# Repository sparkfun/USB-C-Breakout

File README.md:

SparkFun USB-C Serial Breakout
========================================

[*SparkFun Serial Basic Breakout [BOB-15100]*](https://www.sparkfun.com/products/15100)

This is a simple breakout for the USB-C connector.  USB-C is able to
provide up to 1.5 Amps of power and unlike its predecessor is
_reversable_, meaning you won't ever plug a cable in wrong again. 

Repository Contents
-------------------

* **/Hardware** - Eagle design files (.brd, .sch)
* **/Production** - Production panel files (.brd)

License Information
-------------------

This product is _**open source**_! 

Distributed as-is; no warranty is given.

- Your friends at SparkFun.

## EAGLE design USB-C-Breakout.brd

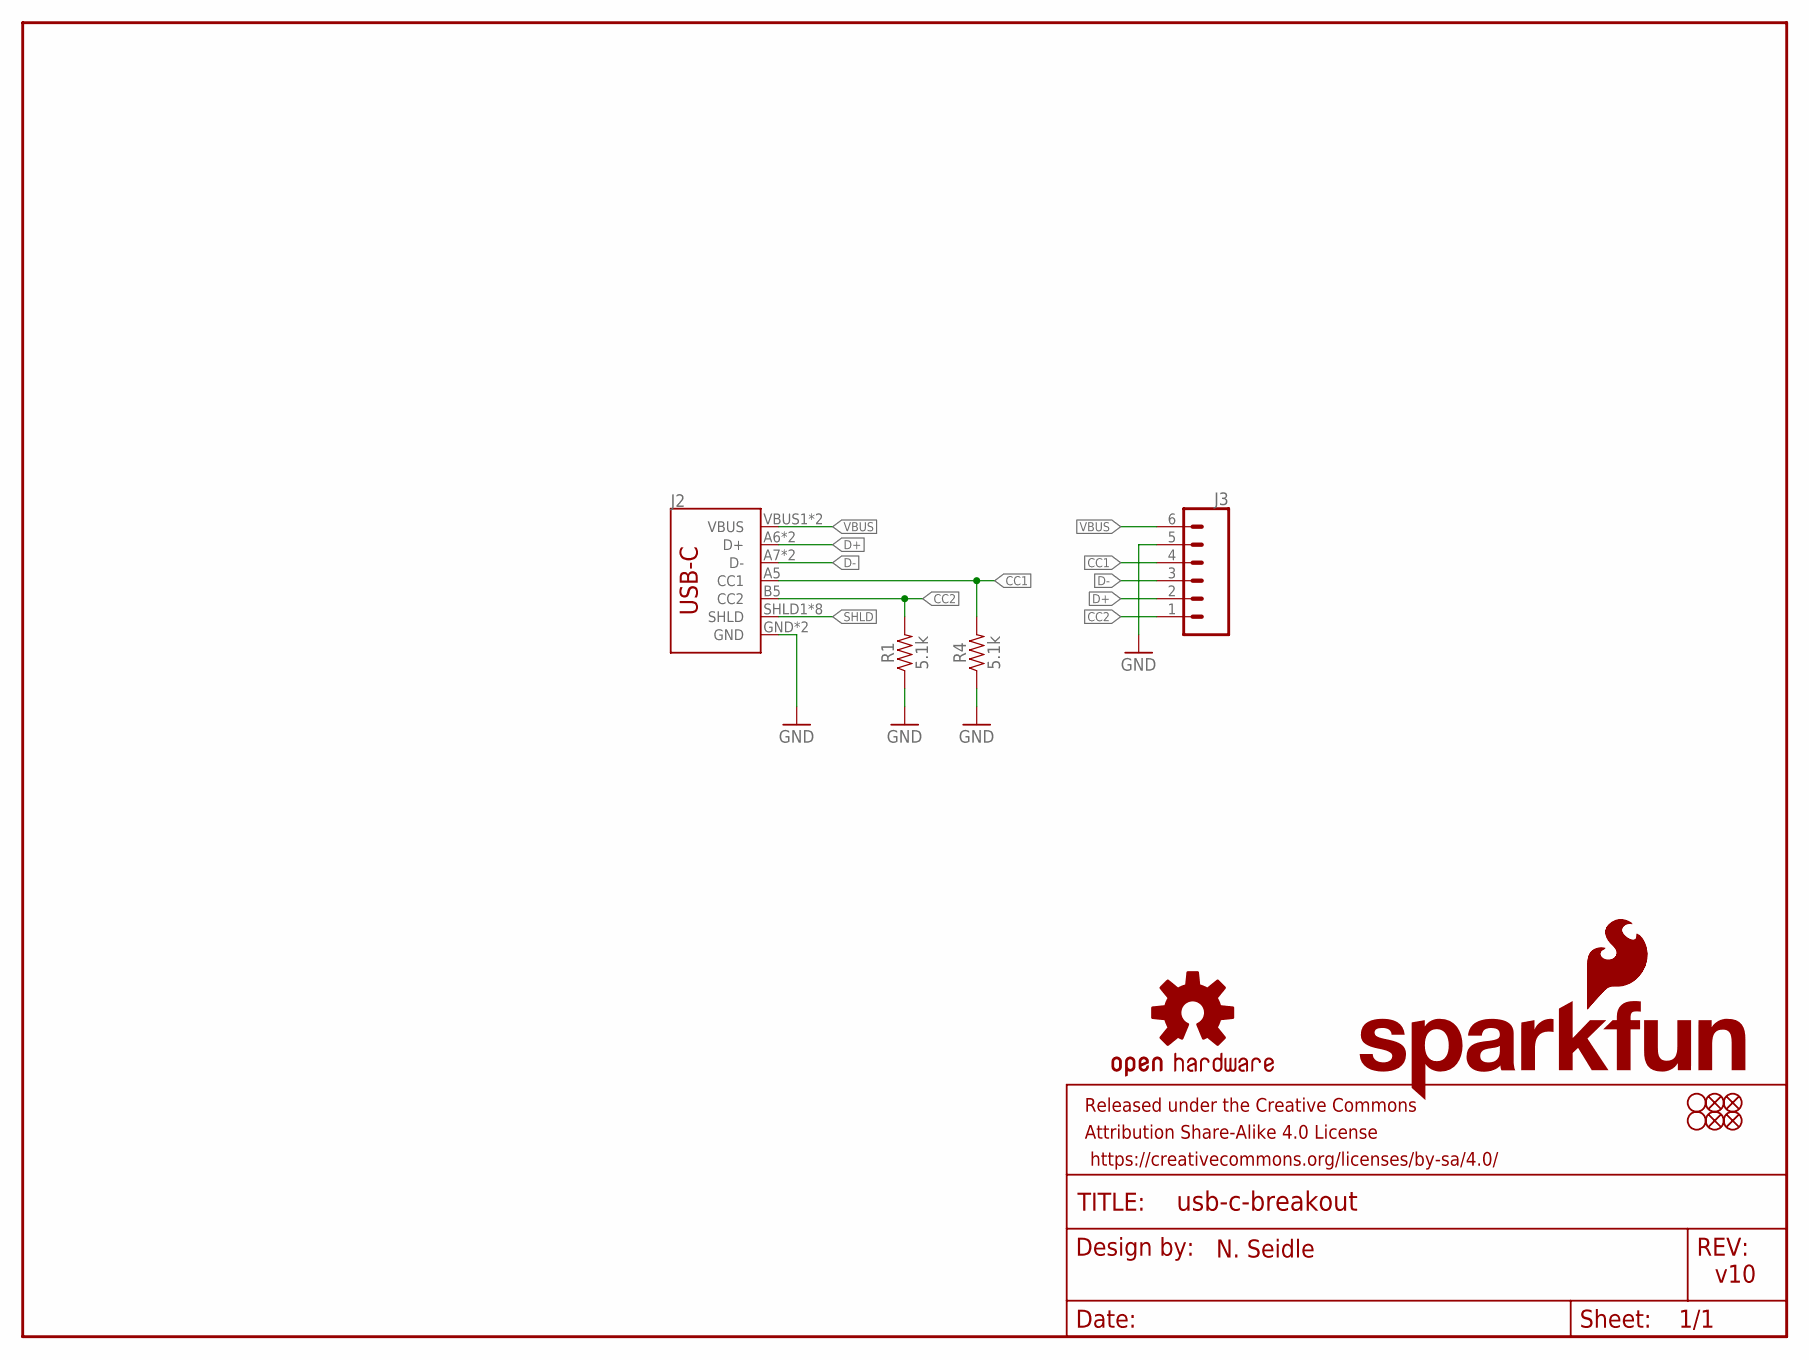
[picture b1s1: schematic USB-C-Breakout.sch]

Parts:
FRAME1: FRAME-LETTER; CREATIVE_COMMONS
H1, H2: STAND-OFF
J2: USB_C16PIN; USB-C-16P
J3: CONN_06NO_SILK_NO_POP; 1X06_NO_SILK
JP3, JP4, JP5, JP6: FIDUCIAL1X2; FIDUCIAL-1X2
LOGO1: OSHW-LOGOS; OSHW-LOGO-S
LOGO2: SFE_LOGO_FLAME.1_INCH; SFE_LOGO_FLAME_.1
LOGO4: SFE_LOGO_NAME_FLAME.1_INCH; SFE_LOGO_NAME_FLAME_.1
R1, R4: 5.1k; 0603

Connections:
CC1: J2.A5 (CC1), J3.4, R4.2
CC2: J2.B5 (CC2), J3.1, R1.2
D+: J2.A6 (D+), J2.B6 (D+), J3.2
D-: J2.A7 (D-), J2.B7 (D-), J3.3
GND: J2.GND, J2.GND2 (GND), J3.5, R1.1, R4.1
SHLD: J2.SHLD1 (SHLD), J2.SHLD2 (SHLD), J2.SHLD3 (SHLD), J2.SHLD4 (SHLD), J2.SHLD5 (SHLD), J2.SHLD6 (SHLD), J2.SHLD7 (SHLD), J2.SHLD8 (SHLD)
VBUS: J2.VBUS1 (VBUS), J2.VBUS2 (VBUS), J3.6

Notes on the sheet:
v10
N. Seidle

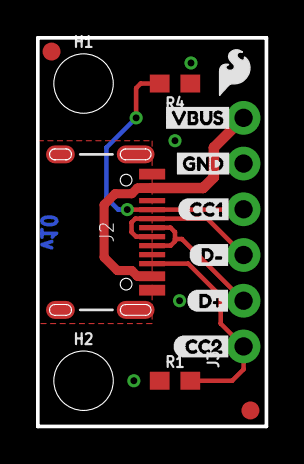
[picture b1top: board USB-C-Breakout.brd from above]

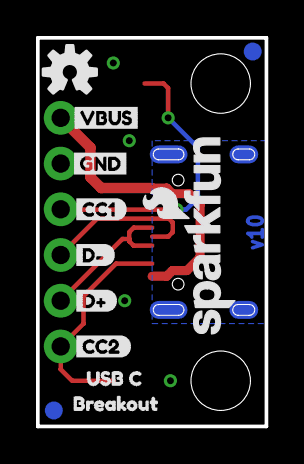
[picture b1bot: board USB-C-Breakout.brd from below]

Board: 2 copper layers, 12.7 x 21.6 mm, 28 parts (12 on the bottom side), 7 nets.

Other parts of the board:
U$1, U$11: GND2
U$2: BREAKOUT1
U$3: CC10
U$4: CC14
U$5: CC21
U$6: CC25
U$7: D#6
U$8: D#7
U$9: D#8
U$10: D#9
U$12, U$13: VBUS3
U$14: USB_C0

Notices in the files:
parts and their libraries:
SparkFun-Aesthetics: Licensing: CC v3.0 Share-Alike You are welcome to use this library for commercial purposes.
SparkFun-Connectors: Licensing: Creative Commons ShareAlike 4.0 International - https://creativecommons.org/licenses/by-sa/4.0
SparkFun-Aesthetics: Released under the Creative Commons
